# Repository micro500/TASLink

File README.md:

TASLink is a series of hardware and supporting software built around the Papilio Pro FPGA development board designed for interfacing with consoles. The hardware is in the form of "wings" (or "shields") that can be attached depending on the situation. There is currently hardware for NES/SNES and the N64.

### NES/SNES

This board supports up to 4 separate consoles simultaneously. 

This board supports SNES multitap on 1 console.

### NES/SNES Cables

Cables were built with Eurocable brand CAT5 which is foil+braided shielded with a thick jacket. Heatshrink was added for extra strain relief.

### NES Visualization

### N64

This prototype board supports basic TAS playback and some more advanced features.

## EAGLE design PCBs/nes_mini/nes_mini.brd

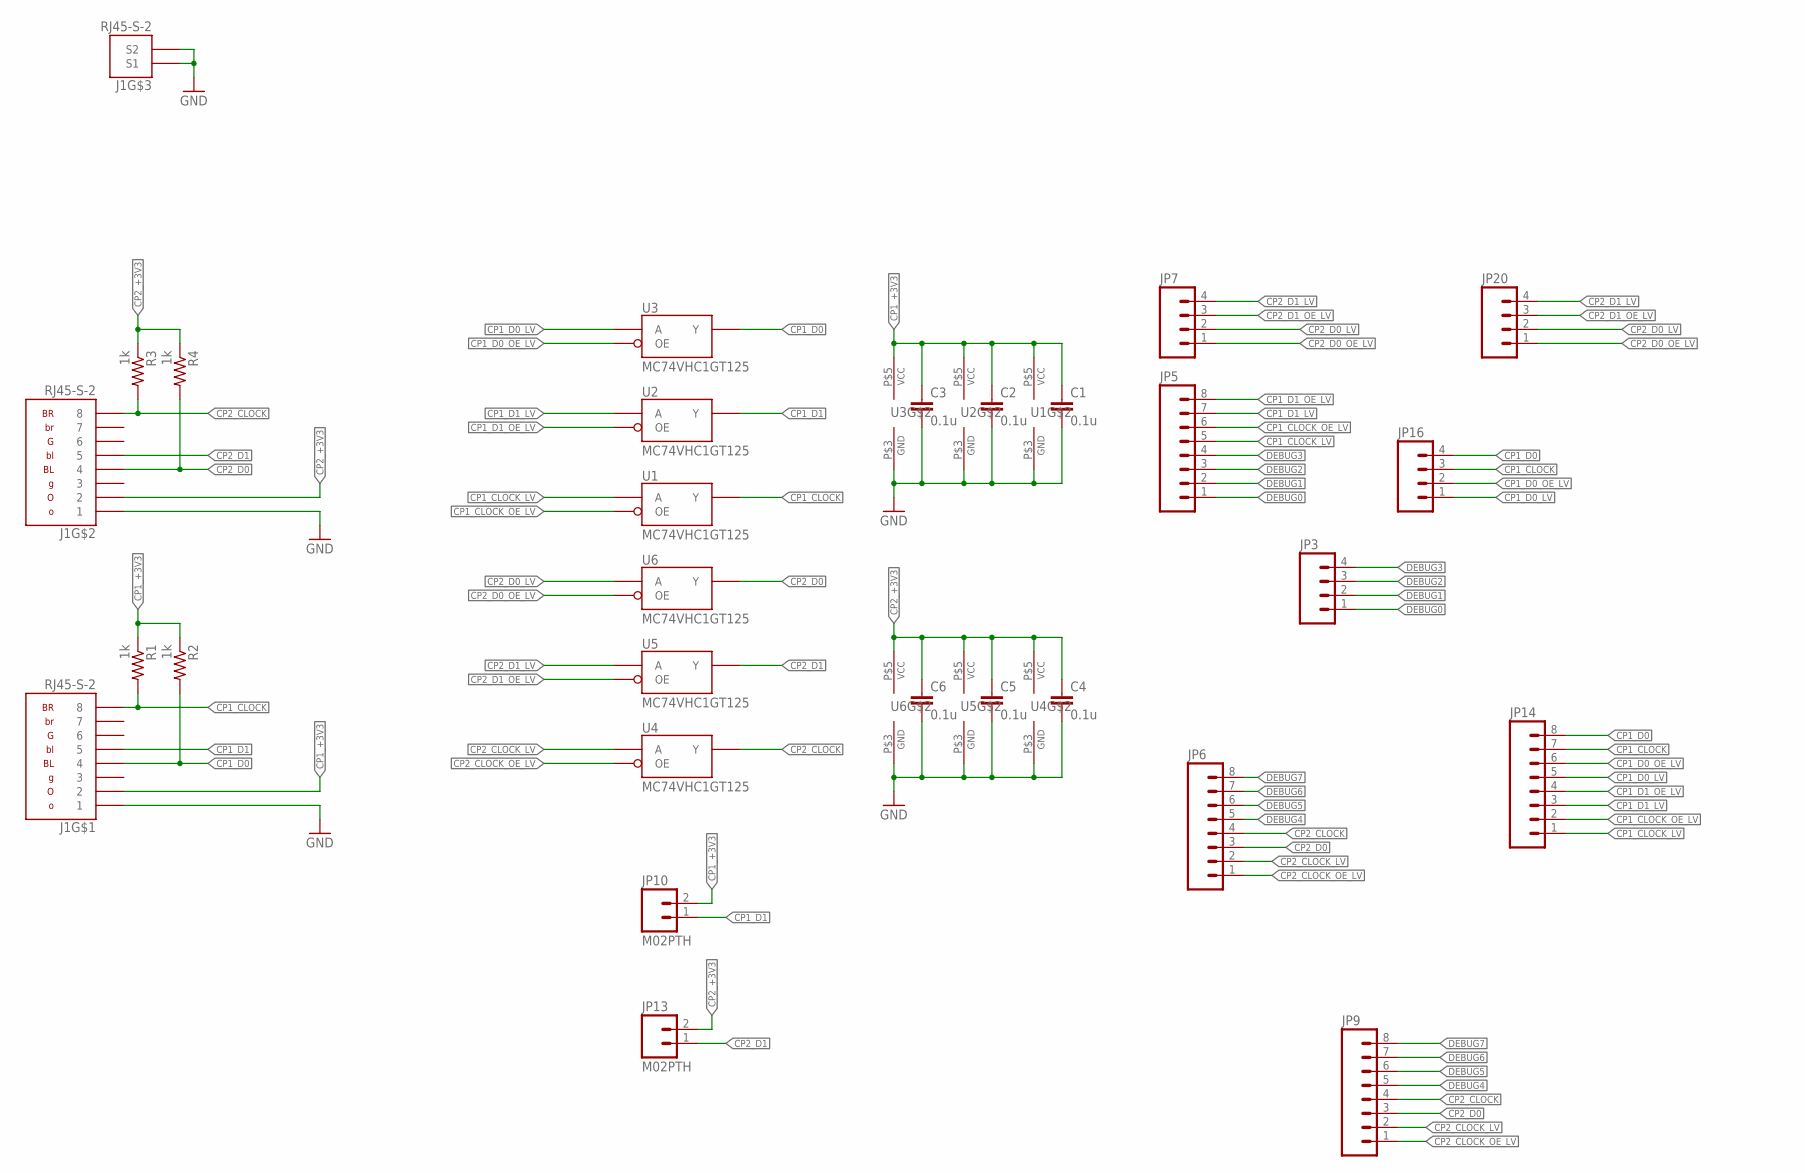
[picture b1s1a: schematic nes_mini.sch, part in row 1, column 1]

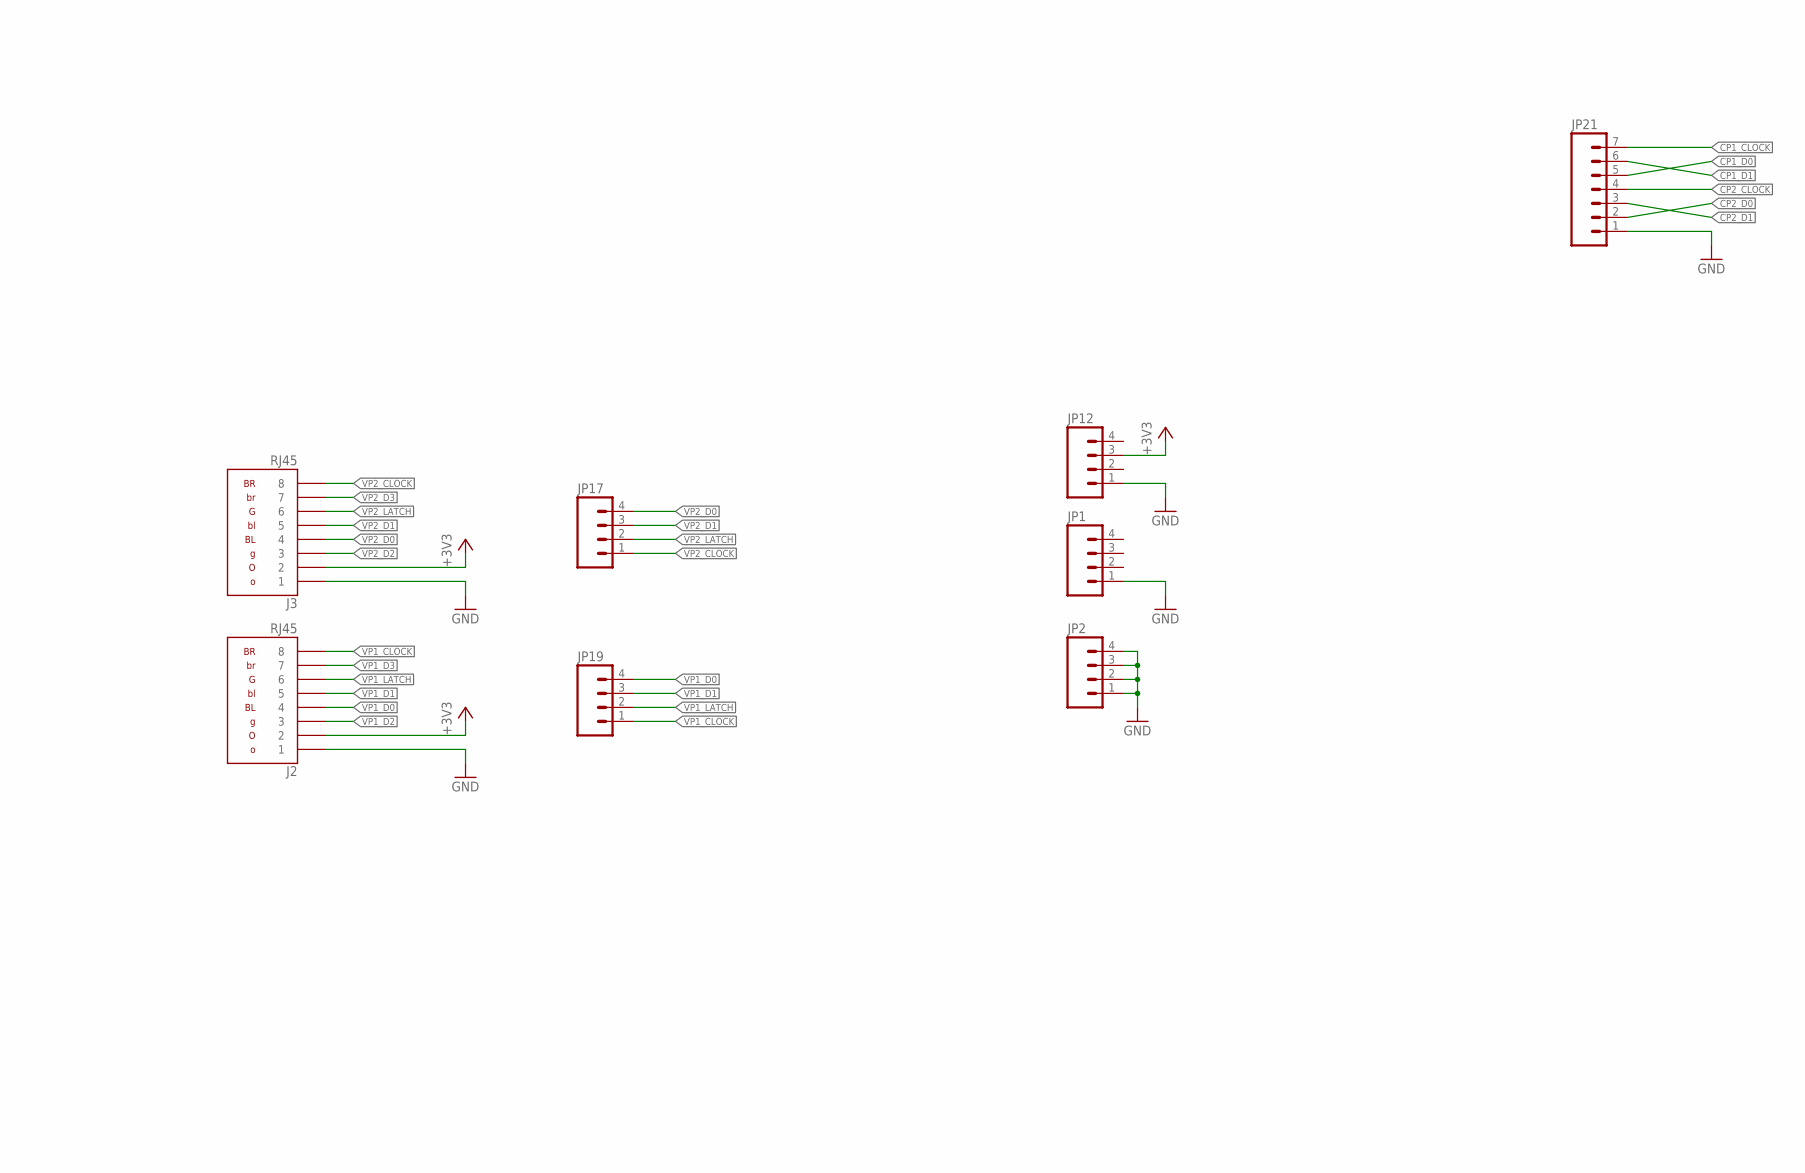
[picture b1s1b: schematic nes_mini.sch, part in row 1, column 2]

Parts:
C1, C2, C3, C4, C5, C6: 0.1u; C0603
J1: RJ45-S-2
J2, J3: RJ45
JP1, JP2, JP3, JP7, JP12, JP16, JP17, JP19, JP20: M04PTH; 1X04
JP5, JP6, JP9, JP14: M081X08; 1X08
JP10, JP13: M02PTH; 1X02
JP21: M07; 1X07
R1, R2, R3, R4: 1k; 0207/2V
U1, U2, U3, U4, U5, U6: MC74VHC1GT125; TSOP-5

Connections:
+3V3: J2.2, J3.2, JP12.3
CP1_+3V3: C1.1, C2.1, C3.1, J1.1-2 (2), JP10.2, R1.1, R2.1, U1.P$5 (VCC), U2.P$5 (VCC), U3.P$5 (VCC)
CP1_CLOCK: J1.1-8 (8), JP14.7, JP16.3, JP21.7, R1.2, U1.P$4 (Y)
CP1_CLOCK_LV: JP5.5, JP14.1, U1.P$2 (A)
CP1_CLOCK_OE_LV: JP5.6, JP14.2, U1.P$1 (OE)
CP1_D0: J1.1-4 (4), JP14.8, JP16.4, JP21.5, R2.2, U3.P$4 (Y)
CP1_D0_LV: JP14.5, JP16.1, U3.P$2 (A)
CP1_D0_OE_LV: JP14.6, JP16.2, U3.P$1 (OE)
CP1_D1: J1.1-5 (5), JP10.1, JP21.6, U2.P$4 (Y)
CP1_D1_LV: JP5.7, JP14.3, U2.P$2 (A)
CP1_D1_OE_LV: JP5.8, JP14.4, U2.P$1 (OE)
CP2_+3V3: C4.1, C5.1, C6.1, J1.2-2 (2), JP13.2, R3.1, R4.1, U4.P$5 (VCC), U5.P$5 (VCC), U6.P$5 (VCC)
CP2_CLOCK: J1.2-8 (8), JP6.4, JP9.4, JP21.4, R3.2, U4.P$4 (Y)
CP2_CLOCK_LV: JP6.2, JP9.2, U4.P$2 (A)
CP2_CLOCK_OE_LV: JP6.1, JP9.1, U4.P$1 (OE)
CP2_D0: J1.2-4 (4), JP6.3, JP9.3, JP21.2, R4.2, U6.P$4 (Y)
CP2_D0_LV: JP7.2, JP20.2, U6.P$2 (A)
CP2_D0_OE_LV: JP7.1, JP20.1, U6.P$1 (OE)
CP2_D1: J1.2-5 (5), JP13.1, JP21.3, U5.P$4 (Y)
CP2_D1_LV: JP7.4, JP20.4, U5.P$2 (A)
CP2_D1_OE_LV: JP7.3, JP20.3, U5.P$1 (OE)
DEBUG0: JP3.1, JP5.1
DEBUG1: JP3.2, JP5.2
DEBUG2: JP3.3, JP5.3
DEBUG3: JP3.4, JP5.4
DEBUG4: JP6.5, JP9.5
DEBUG5: JP6.6, JP9.6
DEBUG6: JP6.7, JP9.7
DEBUG7: JP6.8, JP9.8
GND: C1.2, C2.2, C3.2, C4.2, C5.2, C6.2, J1.1-1 (1), J1.2-1 (1), J1.S1, J1.S2, J2.1, J3.1, JP1.1, JP2.1, JP2.2, JP2.3, JP2.4, JP12.1, JP21.1, U1.P$3 (GND), U2.P$3 (GND), U3.P$3 (GND), U4.P$3 (GND), U5.P$3 (GND), U6.P$3 (GND)
VP1_CLOCK: J2.8, JP19.1
VP1_D0: J2.4, JP19.4
VP1_D1: J2.5, JP19.3
VP1_D2: J2.3
VP1_D3: J2.7
VP1_LATCH: J2.6, JP19.2
VP2_CLOCK: J3.8, JP17.1
VP2_D0: J3.4, JP17.4
VP2_D1: J3.5, JP17.3
VP2_D2: J3.3
VP2_D3: J3.7
VP2_LATCH: J3.6, JP17.2

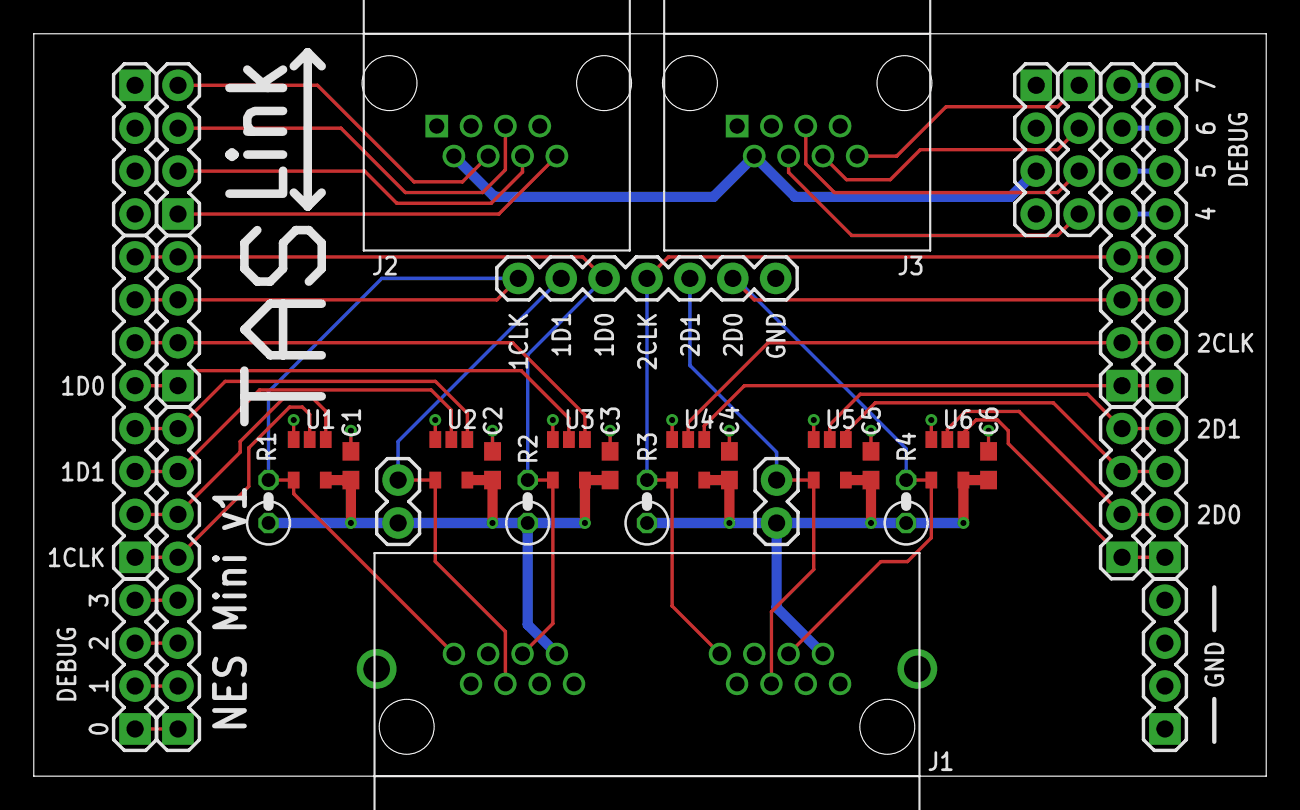
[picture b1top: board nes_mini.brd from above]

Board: 2 copper layers, 72.9 x 43.9 mm, 35 parts (0 on the bottom side), 38 nets.

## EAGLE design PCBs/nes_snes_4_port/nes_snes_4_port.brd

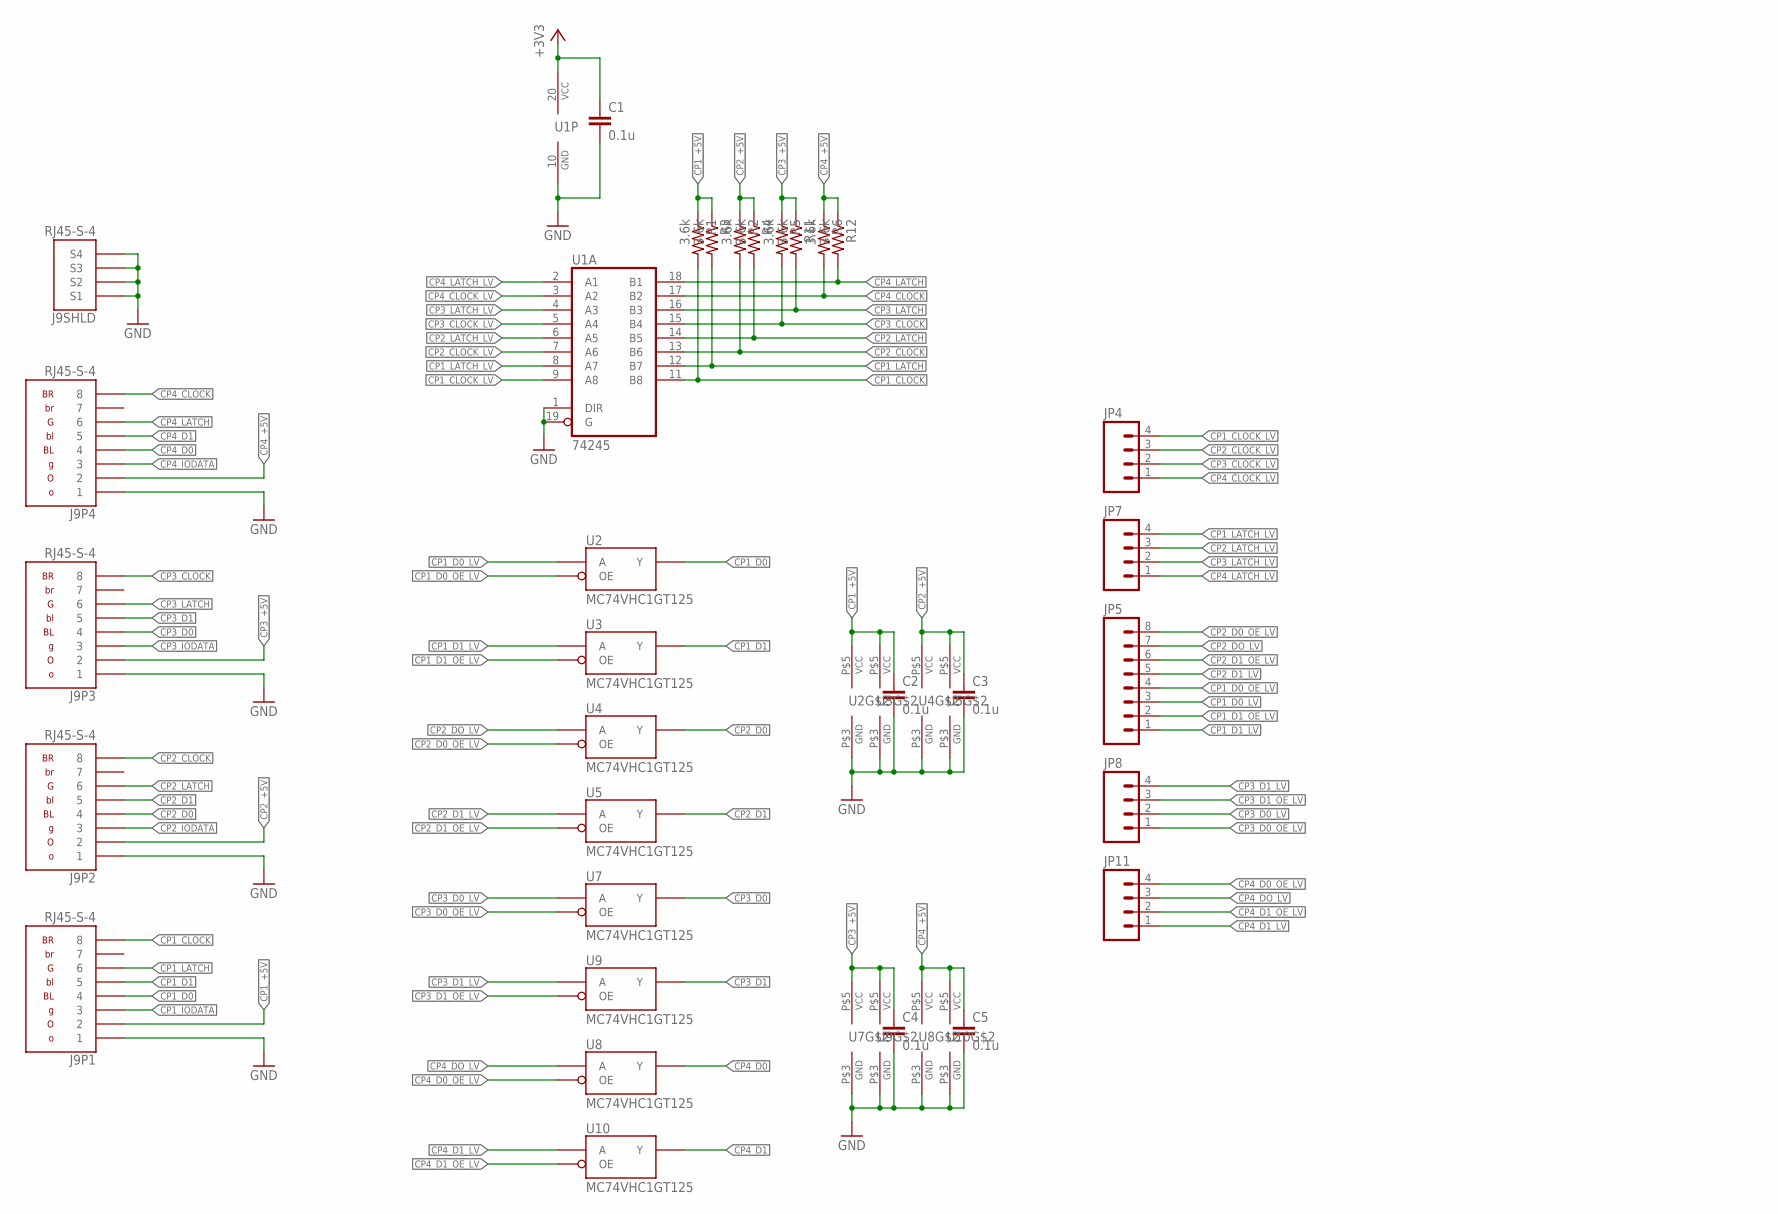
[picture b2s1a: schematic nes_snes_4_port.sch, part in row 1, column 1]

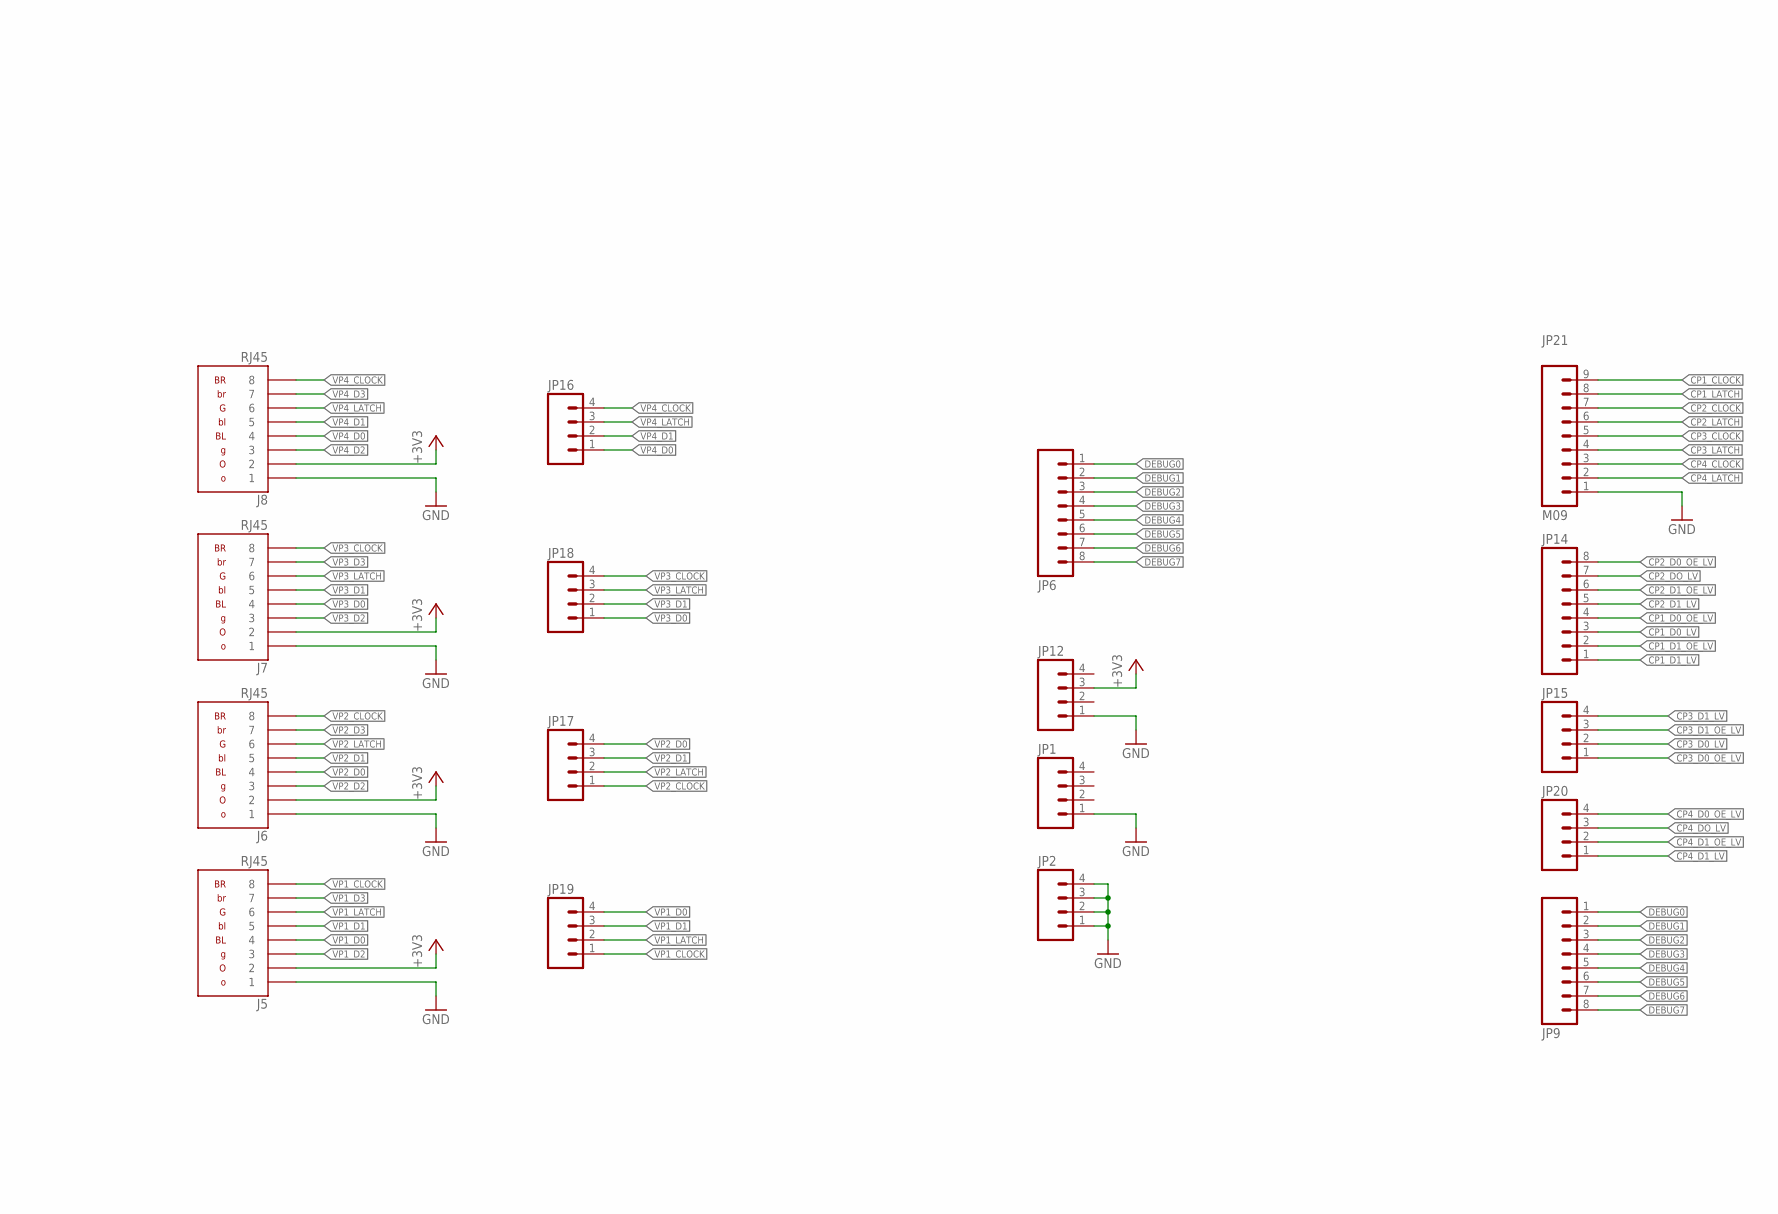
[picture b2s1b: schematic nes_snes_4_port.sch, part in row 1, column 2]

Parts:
C1, C2, C3, C4, C5: 0.1u; C0603
J5, J6, J7, J8: RJ45
J9: RJ45-S-4
JP1, JP2, JP4, JP7, JP8, JP11, JP12, JP15, JP16, JP17, JP18, JP19, JP20: M04PTH; 1X04
JP5, JP6, JP9, JP14: M081X08; 1X08
JP21: M09; 1X09
R1, R2, R3, R4, R5, R6, R11, R12: 3.6k; 0207/2V
U1: 74245; DIL20
U2, U3, U4, U5, U7, U8, U9, U10: MC74VHC1GT125; TSOP-5

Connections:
+3V3: C1.1, J5.2, J6.2, J7.2, J8.2, JP12.3, U1.20 (VCC)
CP1_+5V: C2.1, J9.1-2 (2), R1.1, R3.1, U2.P$5 (VCC), U3.P$5 (VCC)
CP1_CLOCK: J9.1-8 (8), JP21.9, R1.2, U1.11 (B8)
CP1_CLOCK_LV: JP4.4, U1.9 (A8)
CP1_D0: J9.1-4 (4), U2.P$4 (Y)
CP1_D0_LV: JP5.3, JP14.3, U2.P$2 (A)
CP1_D0_OE_LV: JP5.4, JP14.4, U2.P$1 (OE)
CP1_D1: J9.1-5 (5), U3.P$4 (Y)
CP1_D1_LV: JP5.1, JP14.1, U3.P$2 (A)
CP1_D1_OE_LV: JP5.2, JP14.2, U3.P$1 (OE)
CP1_IODATA: J9.1-3 (3)
CP1_LATCH: J9.1-6 (6), JP21.8, R3.2, U1.12 (B7)
CP1_LATCH_LV: JP7.4, U1.8 (A7)
CP2_+5V: C3.1, J9.2-2 (2), R2.1, R4.1, U4.P$5 (VCC), U5.P$5 (VCC)
CP2_CLOCK: J9.2-8 (8), JP21.7, R2.2, U1.13 (B6)
CP2_CLOCK_LV: JP4.3, U1.7 (A6)
CP2_D0: J9.2-4 (4), U4.P$4 (Y)
CP2_D0_OE_LV: JP5.8, JP14.8, U4.P$1 (OE)
CP2_D1: J9.2-5 (5), U5.P$4 (Y)
CP2_D1_LV: JP5.5, JP14.5, U5.P$2 (A)
CP2_D1_OE_LV: JP5.6, JP14.6, U5.P$1 (OE)
CP2_DO_LV: JP5.7, JP14.7, U4.P$2 (A)
CP2_IODATA: J9.2-3 (3)
CP2_LATCH: J9.2-6 (6), JP21.6, R4.2, U1.14 (B5)
CP2_LATCH_LV: JP7.3, U1.6 (A5)
CP3_+5V: C4.1, J9.3-2 (2), R5.1, R11.1, U7.P$5 (VCC), U9.P$5 (VCC)
CP3_CLOCK: J9.3-8 (8), JP21.5, R5.2, U1.15 (B4)
CP3_CLOCK_LV: JP4.2, U1.5 (A4)
CP3_D0: J9.3-4 (4), U7.P$4 (Y)
CP3_D0_LV: JP8.2, JP15.2, U7.P$2 (A)
CP3_D0_OE_LV: JP8.1, JP15.1, U7.P$1 (OE)
CP3_D1: J9.3-5 (5), U9.P$4 (Y)
CP3_D1_LV: JP8.4, JP15.4, U9.P$2 (A)
CP3_D1_OE_LV: JP8.3, JP15.3, U9.P$1 (OE)
CP3_IODATA: J9.3-3 (3)
CP3_LATCH: J9.3-6 (6), JP21.4, R11.2, U1.16 (B3)
CP3_LATCH_LV: JP7.2, U1.4 (A3)
CP4_+5V: C5.1, J9.4-2 (2), R6.1, R12.1, U8.P$5 (VCC), U10.P$5 (VCC)
CP4_CLOCK: J9.4-8 (8), JP21.3, R6.2, U1.17 (B2)
CP4_CLOCK_LV: JP4.1, U1.3 (A2)
CP4_D0: J9.4-4 (4), U8.P$4 (Y)
CP4_D0_OE_LV: JP11.4, JP20.4, U8.P$1 (OE)
CP4_D1: J9.4-5 (5), U10.P$4 (Y)
CP4_D1_LV: JP11.1, JP20.1, U10.P$2 (A)
CP4_D1_OE_LV: JP11.2, JP20.2, U10.P$1 (OE)
CP4_DO_LV: JP11.3, JP20.3, U8.P$2 (A)
CP4_IODATA: J9.4-3 (3)
CP4_LATCH: J9.4-6 (6), JP21.2, R12.2, U1.18 (B1)
CP4_LATCH_LV: JP7.1, U1.2 (A1)
DEBUG0: JP6.1, JP9.1
DEBUG1: JP6.2, JP9.2
DEBUG2: JP6.3, JP9.3
DEBUG3: JP6.4, JP9.4
DEBUG4: JP6.5, JP9.5
DEBUG5: JP6.6, JP9.6
DEBUG6: JP6.7, JP9.7
DEBUG7: JP6.8, JP9.8
GND: C1.2, C2.2, C3.2, C4.2, C5.2, J5.1, J6.1, J7.1, J8.1, J9.1-1 (1), J9.2-1 (1), J9.3-1 (1), J9.4-1 (1), J9.S1, J9.S2, J9.S3, J9.S4, JP1.1, JP2.1, JP2.2, JP2.3, JP2.4, JP12.1, JP21.1, U1.1 (DIR), U1.10 (GND), U1.19 (G), U2.P$3 (GND), U3.P$3 (GND), U4.P$3 (GND), U5.P$3 (GND), U7.P$3 (GND), U8.P$3 (GND), U9.P$3 (GND), U10.P$3 (GND)
VP1_CLOCK: J5.8, JP19.1
VP1_D0: J5.4, JP19.4
VP1_D1: J5.5, JP19.3
VP1_D2: J5.3
VP1_D3: J5.7
VP1_LATCH: J5.6, JP19.2
VP2_CLOCK: J6.8, JP17.1
VP2_D0: J6.4, JP17.4
VP2_D1: J6.5, JP17.3
VP2_D2: J6.3
VP2_D3: J6.7
VP2_LATCH: J6.6, JP17.2
VP3_CLOCK: J7.8, JP18.4
VP3_D0: J7.4, JP18.1
VP3_D1: J7.5, JP18.2
VP3_D2: J7.3
VP3_D3: J7.7
VP3_LATCH: J7.6, JP18.3
VP4_CLOCK: J8.8, JP16.4
VP4_D0: J8.4, JP16.1
VP4_D1: J8.5, JP16.2
VP4_D2: J8.3
VP4_D3: J8.7
VP4_LATCH: J8.6, JP16.3

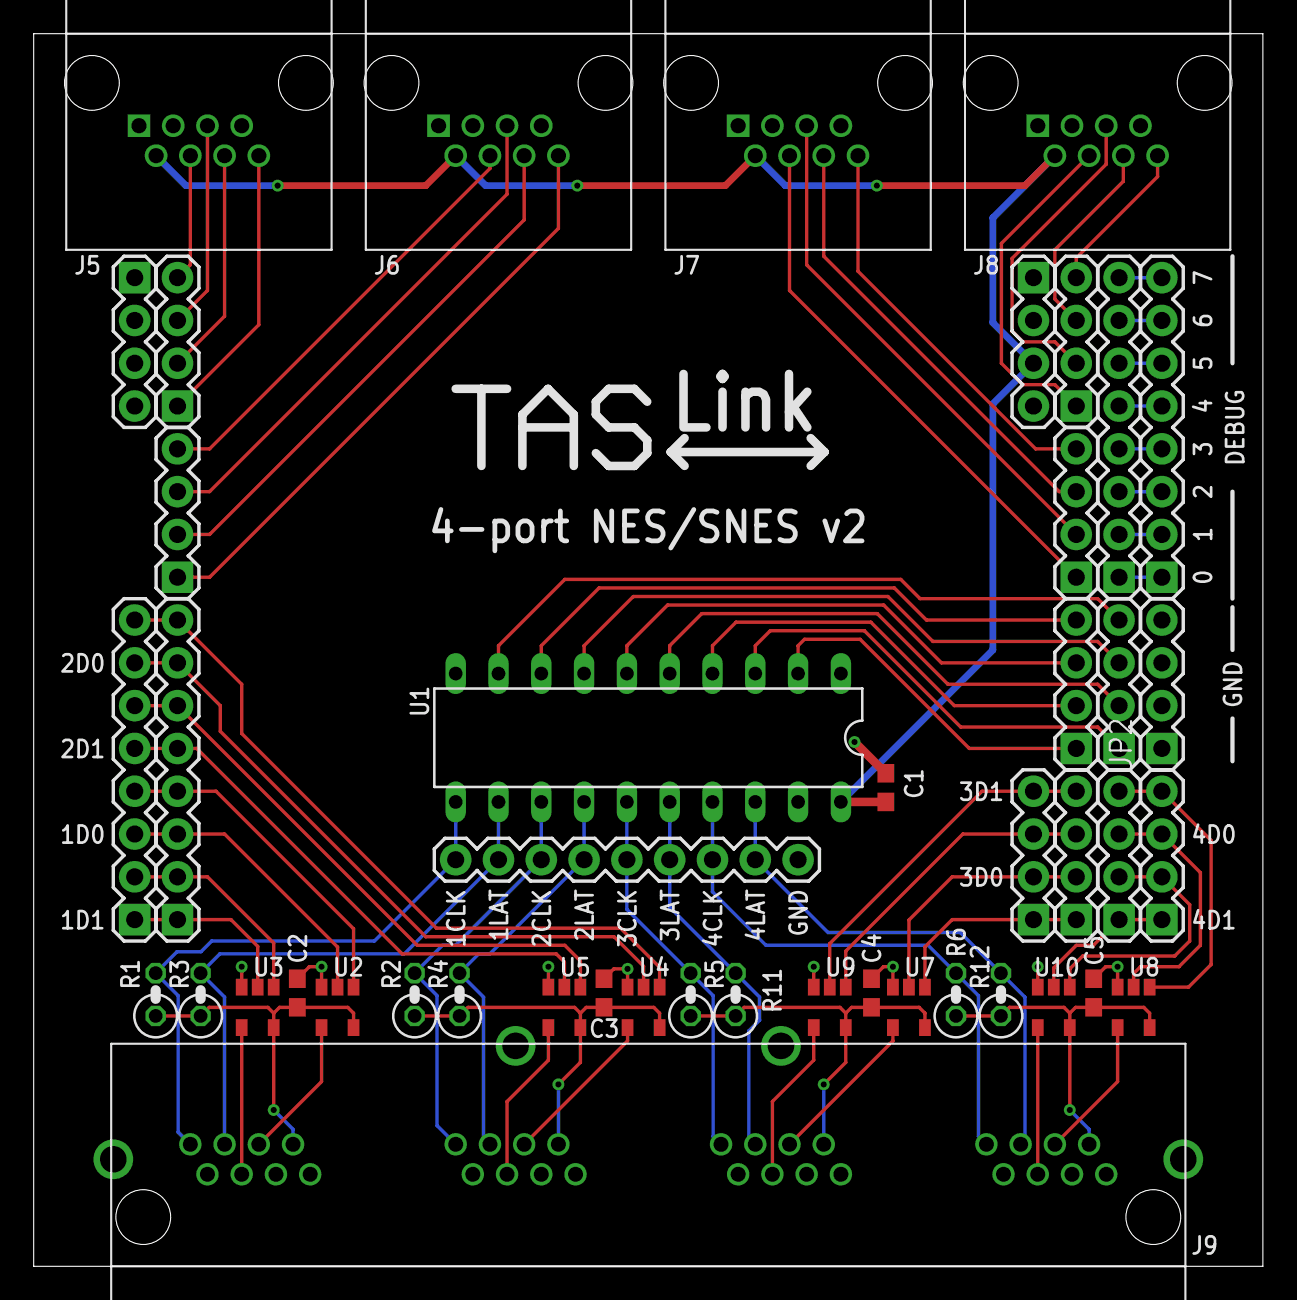
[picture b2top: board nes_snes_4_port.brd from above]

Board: 2 copper layers, 72.9 x 73.2 mm, 45 parts (0 on the bottom side), 70 nets.

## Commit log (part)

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2016-01-26 Adding the starting project and VHDL, enough for two player NES playback.
2016-01-27 Started work on a simple NES/SNES board
2016-01-29 Cleaned up the routing and board layout
2016-02-02 Added name/value labels to the 3.3v to 5v level shifter.
2016-02-02 Added a tap for all the 5v lines from the console. Fixed part labels. Added more labeling. Added a logo. Cleaned up the schematic.
2016-02-26 Updated the constraints file for the new PCB pinout
2016-02-26 Removed the old shift register.
2016-02-26 Renamed the new shift register file.
2016-02-26 Fixed the project to actually compile.
2016-02-26 Added a module to handle delaying a clock signal.
2016-02-27 Renamed the raw data lines. Removed old comments, added some new ones.
2016-02-27 Renamed the remaining signals to remove the "nes" naming. Added signal toggles for p2.
2016-02-27 Added a serial in line to the shift register to allow changing the overread value.
2016-02-27 Adding code for a 32 bit "controller" that can act like an 8, 16, 24, or 32 bit shift register.
2016-02-28 Updated the design to use the new controller implementation. It is currently set up for 2 player NES.
2016-02-29 Used generators to create the 8 controllers.
2016-03-02 Added a single multitap component and wired it in.
2016-03-02 Fixed the button_queue usage to allow RAM blocks to be generated.
2016-03-07 Added a second multitap.
2016-03-08 Changed the console interface pins to std logic vectors and cleaned up the constraints file to match. Used generators to create a few more repetitive modules.
2016-03-15 Added a fifo component to hold the data for each controller.
2016-03-17 Changed the serial communication to allow changing more settings and feeding in more data. Controller size is now changeable for each controller.
2016-03-17 Increased the UART speed to 2Mbaud.
2016-03-18 Resized the fifo to 64 frames.
2016-03-19 Changed the port config command to be per port. Fixed the signal routing for every port mode. Added an option to enable a clock delay (for SMB3 type games). Fixed the clock delay module to work. Fixe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
2016-03-19 Removed the old clock delay from the shift register module.
2016-03-19 Added custom commands to allow only sending specific controllers per frame to reduce packet sizes.
2016-04-07 Cloned the simple NES/SNES board to start a 4 port version
2016-04-11 Lots of work on the 4 port PCB. Added some shielded RJ45s to the library.
2016-04-12 4 port PCB: Cleaned up the schematic.
2016-04-12 4 port PCB: Cleaned up the silkscreen.
2016-04-12 4 port PCB: Scaled up the TASLink logo to better fill the empty space.
2016-04-12 4 port PCB: Added a title to the silkscreen.
2016-04-12 4 port PCB: Tweaked some component labels.
2016-04-12 4 port PCB: Added a version number.
2016-04-13 Cloned the 4 port NES/SNES PCB to start an N64 PCB.
2016-04-14 PCB Library: Made the pins on the RJ45 symbol swappable.
2016-04-14 N64 pcb: Schematic complete and board routed.
2016-04-23 Adding a NES visualization board designed to fit in a TTX controller shell.
2016-04-23 NES Visualization: Changed the reference resistor to 0805 size.
2016-04-23 NES Visualization: Replaced a drill hit near the edge with a slot.
2016-04-30 Added support for events which advance the data lanes and signal the computer via the serial port. Changed the ucf to the 4 port PCB design. Commented out IO support for now.
2016-04-30 Expanded the design to 4 console ports and 4 events.
2016-05-04 Adding a breakout board for the visualization hardware.
2016-05-04 Adding .gitignore
2016-05-04 Visualization breakout: Adding a cam file.
2016-05-10 Adding a PCB to tap a controller line
2016-05-27 Added a .gitignore for movie files.
2016-05-27 Added support for (NES) visualization. Added support to route TX to a debug pin. Added support to configure console ports 3 and 4.
2016-05-28 Adding a basic N64 HDL project.
2016-06-04 N64: Renamed some signals to be a little less confusing.
2016-06-04 N64: Moved the byte receiving code into a separate module.
2016-06-14 N64: Added a module to handle sending up to 32 bytes.
2016-06-18 N64: Adding some MITM N64 code that is partially functional.
2016-06-24 N64 MITM: Now able to intercept some commands and respond instead of the controller.
2016-06-26 Filling in the readme a bit
2016-06-28 Started a wxpython UI
2016-06-29 hopefully supports multiple simultaneous runs
    need to confirm with hardware
2016-06-29 uploaded to wrong folder
2016-06-29 hopefully supports multiple simultaneous runs
    need to confirm on hardware
2016-06-29 supports single load/save [alpha]
    further save/load functionality coming ASAP
2016-06-29 Condense some assignments
2016-06-29 Simplify claimConsolePort and releaseConsolePort
    Working under the assumption that value pairs for type and port arguments
    will never cause an IndexError when accessing consoleLanes... but that was
    sort of already the case
2016-06-29 Remove a couple unused things
2016-06-29 Condense several if blocks
    I also caught a typo.
2016-06-29 Delete TASRun.py
    This file has been merged into TASLink.py
2016-06-30 check for port conflicts on load
    additionally:
    - removed a customEvents list which was always equivalent to the customStreams list
    - removed the customEvent class variable from TASRun since it is managed by the driver
2016-06-30 Delete TASLink.py
    uploaded to wrong folder.. .again! (git nub)
2016-06-30 hopefully supports multiple runs
2016-06-30 attempt to fix serial communication
2016-06-30 added end command to end runs
    also added single-letter options for 'normal' 'multitap' and 'four-score' options
2016-06-30 fixed getInputBuffer
    off-by-one error was causing unused controller data to not be skipped, causing unpredictable run results
2016-06-30 reset command added
2016-06-30 load now takes an optional filename
    to save a step
2016-06-30 autocomplete changes
    - now works perfectly within a command
    - now broken in autocompleting the actual commands
    - '"BUG" FIX: hitting enter no-long repeats the last-given command
2016-07-01 finished autocomplete
2016-07-01 hopefully fixed port map error
2016-07-01 added variable blank initial input frames
2016-07-01 let the user know when the run is ready to begin
2016-07-01 added modify_frames command
2016-07-04 *final* port comm logic fix; clean serial comm
2016-07-04 improved console output
2016-07-04 Adding the SNES visualization boards, SNES ext port board, and replay adapter board.
2016-07-04 mic. small tweaks
2016-07-04 port logic fixes; supports new hardware reset command
2016-07-04 fixed runtime error; moved function definition
2016-07-04 Added a command to reset only certain lanes. Changed the default values for all events to advance no lanes.
2016-07-05 new asks about dpcm_fix. command removed.
2016-07-05 cleaner exiting (hopefully)
2016-07-05 warning added to remove command
2016-07-05 command line loading
2016-07-05 reset all now resets frameCounts
2016-07-05 Adding a 2 port version of the visualization breakout.
2016-07-05 reset all now re-pre-buffers!
2016-07-09 should support faster serial communication
2016-07-09 attempted 'remove' fix; fixed typos
2016-07-19 Visualization now works for SNES as well as NES.
2016-07-30 (hopefully) Fixed SNES support
    allowed for r16 and r16m. also fixed logic error for any controller data large than 1 byte
2016-07-30 made reading ints 'crash-safe'
2016-07-31 now listens on all ports for latch instead of first
2016-08-01 added .strip on file extension check
2016-08-01 now works great with SNES
    NES temporarily broken
2016-08-01 Now fully supports NES and SNES :)
2016-08-01 Now always starts with all events disabled
2016-08-03 Event enabled flag now actually enables/disables the event.
2016-08-03 Added a temporary debug command to allow forcing debug pin 4 to high/low.
2016-08-03 Added a temporary debug command to allow monitoring of the buffer_empty signal for buffer 1 using a visualization board plugged into port 4.
2016-08-04 safe float read, possible crash fix
    1) made reading window value safe from runtime error
    2) runtime error that has only been seen twice upon loading a new run may have been fixed; needs testing
2016-08-06 misc. UI bug fixes
2016-08-06 added the select command. commands now refer to selected run
2016-08-08 Added fair round-robin processing of the events. Fixed the tx_buffer_full signal in the uart to work more logically.
2016-08-08 minor improvements with syntax
2016-08-13 fixed off-by-one error
2016-08-13 fixed a single space which freaks out python
2016-08-13 small 'remove' fix
2016-08-13 fixed select command
2016-09-02 N64 PCB: Added controller ports with switches and mostly routed the board.
2016-09-06 Significantly decreased loading times
2016-09-20 added console_off and console_on commands for SNES
2016-09-20 N64 PCB: Added switches, controller ports, and many other features. Layout and routing mostly complete.
2016-09-20 N64 PCB: Cleaned up the schematic.
2016-09-20 N64 PCB: Small tweaks
2016-09-26 few command changes
2016-10-03 added save/not-saved check, improved display
2016-10-03 NES/SNES 4-port PCB: ERC/DRC errors processed. Removed a part label.
2016-10-03 NES/SNES 4-port PCB: Removed the power supply pins that did nothing. Fixed the backwards power supply pin. Added 4 ground tap pins.
2016-10-16 added add_transition command, bug fixes
2016-10-17 re-organized code, new data structure
2016-10-17 significantly reduced load at idle
2016-10-19 quick bug fix
2017-01-05 Adding current files for the NES Mini
2017-01-06 NES Mini: ucf changes for the new board. Changed to 16 bit buffers to allow for the home button.
2017-10-06 little
2018-04-16 correct function creating a new run and setting the number of dummy frames
2018-04-28 First Attempt at everdrive aware dummy frames
2018-04-28 change to number of frames in everdrive header
2018-04-28 cleanup and fix of process for adding/removing header for starting a everdrive
2018-04-28 add support for adding everdrive on run load/creation
2018-04-29 Quick fix for loading run with everdrive header + dummy frames
2018-04-29 removed redundant if statement
2018-05-03 change of wording on everdrive check in new run
2018-05-10 Add shebang line to python scripts and make executable
    Add shebang for easy execution of python scripts and set the execute
    bit
    Fix typos in TASLink.py comments
2018-05-11 Fix finally typo in TASLink.py
2018-05-13 Add Functionality to generate a Default filename for saved runs
2018-05-13 Make do_save use Default Save Name if no input is given
2018-05-13 Added a Default options config to the top of the script Had to change how reading the inputs when creating a new run is done
2018-06-02 Added functionality to catch missing settings from loaded tcf files
2018-06-03 fix do_restart for dwango
    holding reset for a full second resets sd2snes to menu
2018-06-05 added second restart command
    to do a hard reset of the console
2018-07-21 Add support for triggering a reset of the Console midrun also fixed bug in loading runs that was causing transitions to be discarded on load
2018-07-22 Add a note in do_add_transitions about resets
2018-08-25 Implement support for a SD2SNES header also fixed issue with adding blank frames not accounting for headers
2018-08-31 Add a single blank frame to the end of the input buffer this fixes an issue causing runs to desync if there is an input on the last frame it gets held
2018-09-02 Add command to reload saved run from file see Ownasaurus/TASLink#14
2018-09-02 Add help documentation to commands that dont have any
2018-09-02 Add command to run commands from a file Basic testing indicates it works fairly well I was able to have it load a run List the run and remove it again without issues It can call other commands as wel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
2018-09-16 Starting work on python3 working bit by bit implements get_input() to replace readint,checkint,readfloat,checkfloat
2018-09-16 implemented load()
2018-09-16 Copy most of the code over and start making changes needed for python3
2018-09-17 more fixes
2018-09-19 Commented out a couple of debug commands
2018-09-19 Replaced the rest of the calls to readint/readfloat and raw_input with get_input calls
2018-09-21 Implements notification on end of playback.
2018-10-09 fix emcoding issue for r08 files

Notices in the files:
parts and their libraries:
SparkFun-Connectors: Licensing: CC v3.0 Share-Alike You are welcome to use this library for commercial purposes.
